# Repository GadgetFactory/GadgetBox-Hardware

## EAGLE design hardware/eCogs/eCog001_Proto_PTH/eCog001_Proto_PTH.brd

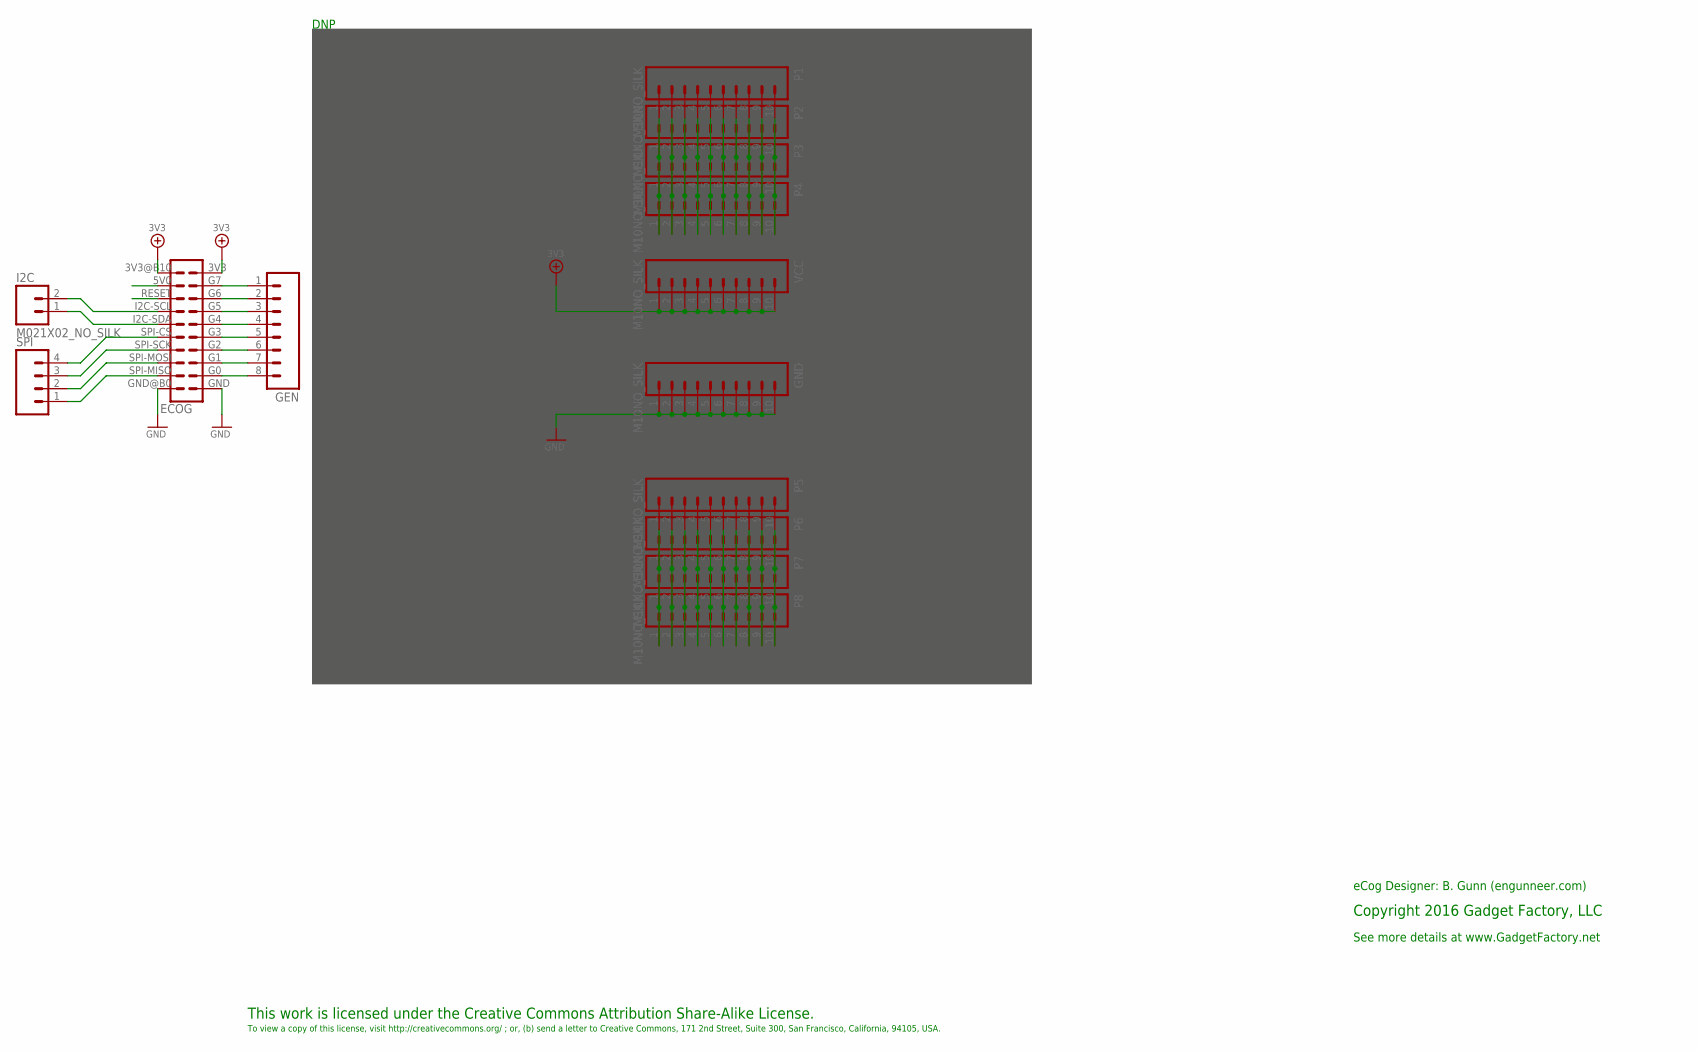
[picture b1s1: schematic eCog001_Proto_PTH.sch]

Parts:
ECOG: ECOG_DUALTHROUGHHOLE; ECOG_DUAL_TH
GEN: M08NO_SILK; 1X08_NO_SILK
GND: M10NO_SILK; 1X10_NO_SILK
I2C: M021X02_NO_SILK; 1X02_NO_SILK
P1, P2, P3, P4, P5, P6, P7, P8: M10NO_SILK; 1X10_NO_SILK
SPI: M041X04_NO_SILK; 1X04_NO_SILK
VCC: M10NO_SILK; 1X10_NO_SILK

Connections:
3V3: ECOG.3V3, ECOG.3V3@B10 (3V3), VCC.1, VCC.2, VCC.3, VCC.4, VCC.5, VCC.6, VCC.7, VCC.8, VCC.9, VCC.10
GND: ECOG.GND, ECOG.GND@B0 (GND), GND.1, GND.2, GND.3, GND.4, GND.5, GND.6, GND.7, GND.8, GND.9, GND.10
unnamed: ECOG.G7, GEN.1
unnamed: ECOG.G6, GEN.2
unnamed: ECOG.G5, GEN.3
unnamed: ECOG.G4, GEN.4
unnamed: ECOG.G3, GEN.5
unnamed: ECOG.G2, GEN.6
unnamed: ECOG.G1, GEN.7
unnamed: ECOG.G0, GEN.8
unnamed: ECOG.SPI-MISO, SPI.1
unnamed: ECOG.SPI-MOSI, SPI.2
unnamed: ECOG.SPI-SCK, SPI.3
unnamed: ECOG.SPI-CS, SPI.4
unnamed: ECOG.I2C-SDA, I2C.1
unnamed: ECOG.I2C-SCL, I2C.2
unnamed: P1.2, P2.2, P3.2, P4.2
unnamed: P1.3, P2.3, P3.3, P4.3
unnamed: P1.4, P2.4, P3.4, P4.4
unnamed: P1.5, P2.5, P3.5, P4.5
unnamed: P1.6, P2.6, P3.6, P4.6
unnamed: P1.7, P2.7, P3.7, P4.7
unnamed: P1.8, P2.8, P3.8, P4.8
unnamed: P1.9, P2.9, P3.9, P4.9
unnamed: P1.10, P2.10, P3.10, P4.10
unnamed: P1.1, P2.1, P3.1, P4.1
unnamed: P5.1, P6.1, P7.1, P8.1
unnamed: P5.2, P6.2, P7.2, P8.2
unnamed: P5.3, P6.3, P7.3, P8.3
unnamed: P5.4, P6.4, P7.4, P8.4
unnamed: P5.5, P6.5, P7.5, P8.5
unnamed: P5.6, P6.6, P7.6, P8.6
unnamed: P5.7, P6.7, P7.7, P8.7
unnamed: P5.8, P6.8, P7.8, P8.8
unnamed: P5.9, P6.9, P7.9, P8.9
unnamed: P5.10, P6.10, P7.10, P8.10

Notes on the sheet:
This work is licensed under the Creative Commons Attribution Share-Alike License.
To view a copy of this license, visit http://creativecommons.org/ ; or, (b) send a letter to Creative Commons, 171 2nd Street, Suite 300, San Francisco, California, 94105, USA.
Copyright 2016 Gadget Factory, LLC
See more details at www.GadgetFactory.net
eCog Designer: B. Gunn (engunneer.com)
DNP

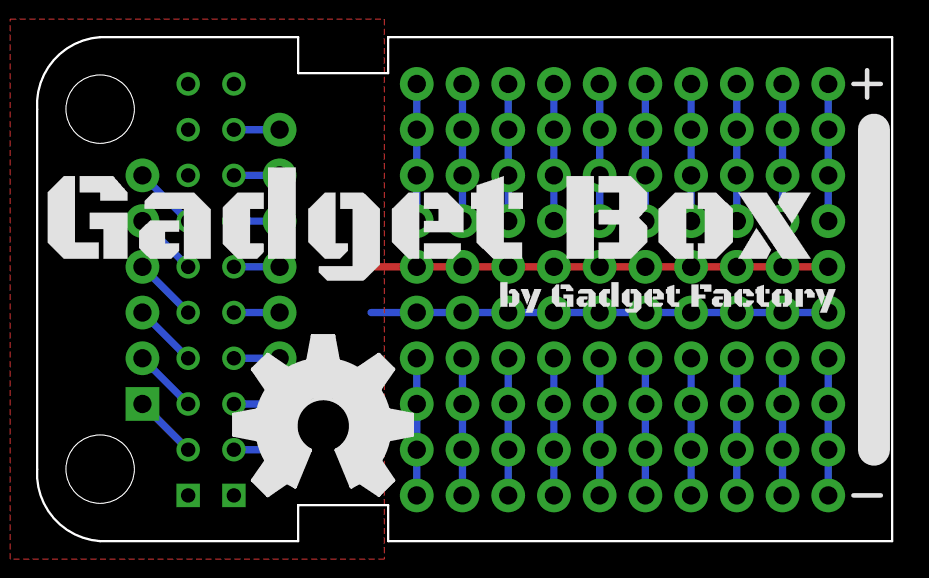
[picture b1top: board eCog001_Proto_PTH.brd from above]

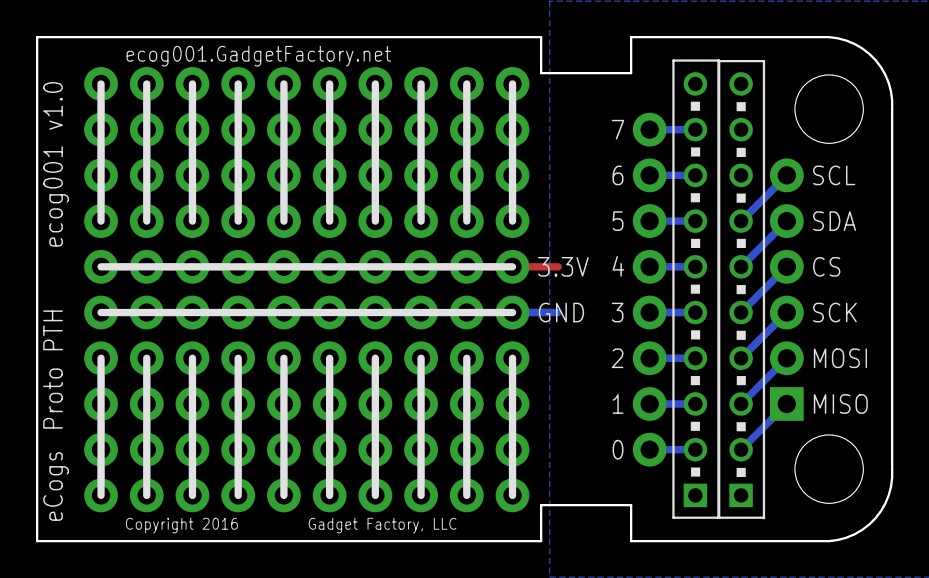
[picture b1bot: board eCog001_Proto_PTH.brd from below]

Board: 2 copper layers, 47.5 x 28.0 mm, 16 parts (2 on the bottom side), 36 nets.

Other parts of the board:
U$1: GADGETBOX_TEXT
U$10: OSHW_FILLX350_NOTEXT

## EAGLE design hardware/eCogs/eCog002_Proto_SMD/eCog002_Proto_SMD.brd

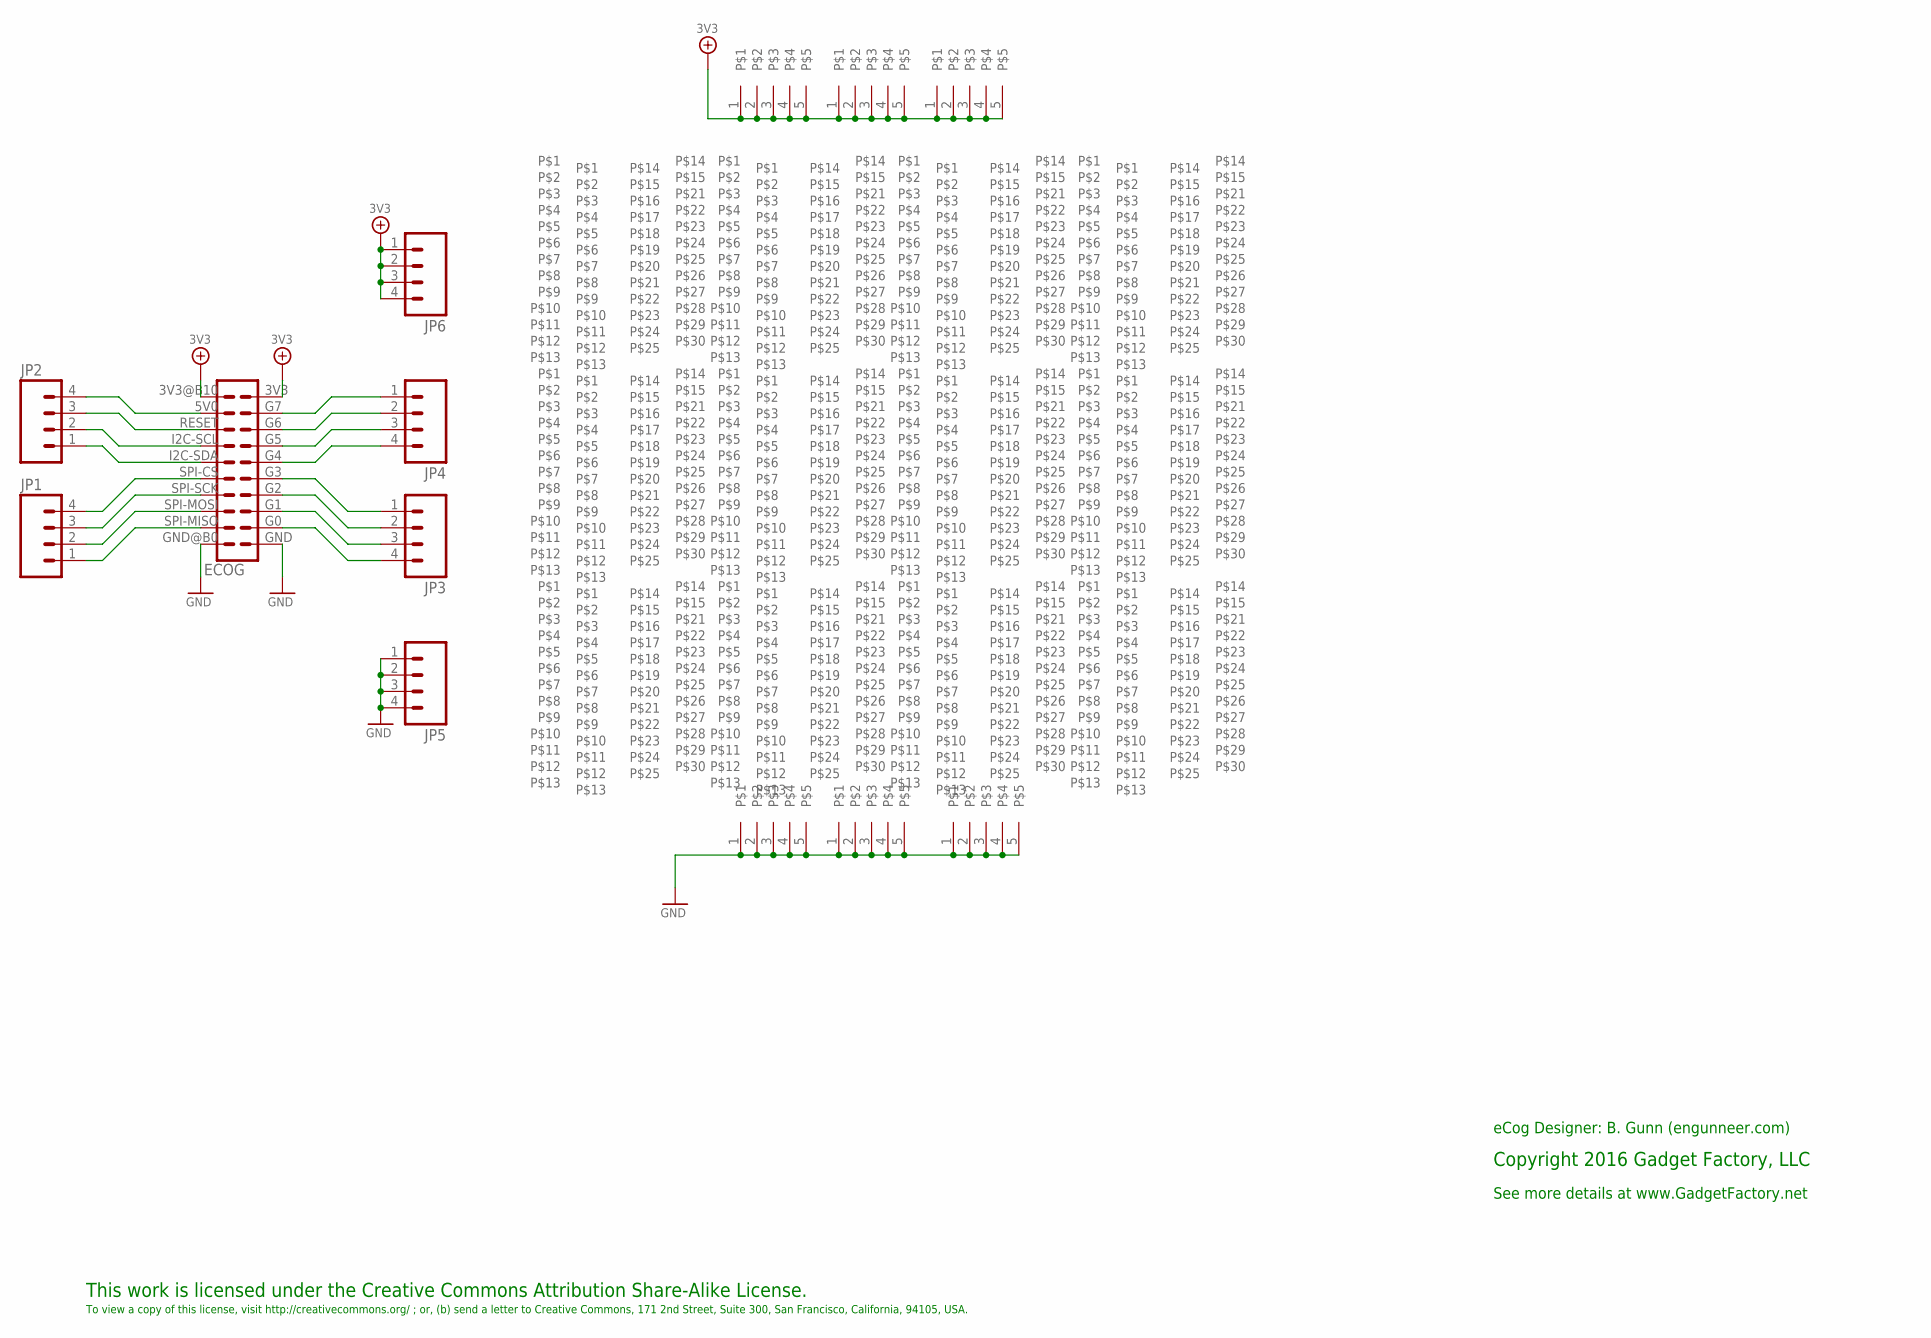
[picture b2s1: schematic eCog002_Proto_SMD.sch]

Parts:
ECOG: ECOG_DUALTHROUGHHOLE; ECOG_DUAL_TH
JP1, JP2, JP3, JP4, JP5, JP6: M041.27MM; 1X04-1.27MM
U$2, U$3, U$4, U$5, U$6, U$7, U$8, U$9, U$11, U$12, U$13, U$14: SMD_PROTO_2550X65; SMD-5065
U$15, U$16, U$17, U$18, U$19, U$20: SMD_PROTO_55; SMD-5065-5

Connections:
3V3: ECOG.3V3, ECOG.3V3@B10 (3V3), JP6.1, JP6.2, JP6.3, JP6.4, U$15.1, U$15.2, U$15.3, U$15.4, U$15.5, U$16.1, U$16.2, U$16.3, U$16.4, U$16.5, U$17.1, U$17.2, U$17.3, U$17.4, U$17.5
GND: ECOG.GND, ECOG.GND@B0 (GND), JP5.1, JP5.2, JP5.3, JP5.4, U$18.1, U$18.2, U$18.3, U$18.4, U$18.5, U$19.1, U$19.2, U$19.3, U$19.4, U$19.5, U$20.1, U$20.2, U$20.3, U$20.4, U$20.5
unnamed: ECOG.G7, JP4.1
unnamed: ECOG.G6, JP4.2
unnamed: ECOG.G5, JP4.3
unnamed: ECOG.G4, JP4.4
unnamed: ECOG.G3, JP3.1
unnamed: ECOG.G2, JP3.2
unnamed: ECOG.G1, JP3.3
unnamed: ECOG.G0, JP3.4
unnamed: ECOG.SPI-MISO, JP1.1
unnamed: ECOG.SPI-MOSI, JP1.2
unnamed: ECOG.SPI-SCK, JP1.3
unnamed: ECOG.SPI-CS, JP1.4
unnamed: ECOG.I2C-SDA, JP2.1
unnamed: ECOG.I2C-SCL, JP2.2
unnamed: ECOG.RESET, JP2.3
unnamed: ECOG.5V0 (5V), JP2.4

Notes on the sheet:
This work is licensed under the Creative Commons Attribution Share-Alike License.
To view a copy of this license, visit http://creativecommons.org/ ; or, (b) send a letter to Creative Commons, 171 2nd Street, Suite 300, San Francisco, California, 94105, USA.
Copyright 2016 Gadget Factory, LLC
See more details at www.GadgetFactory.net
eCog Designer: B. Gunn (engunneer.com)

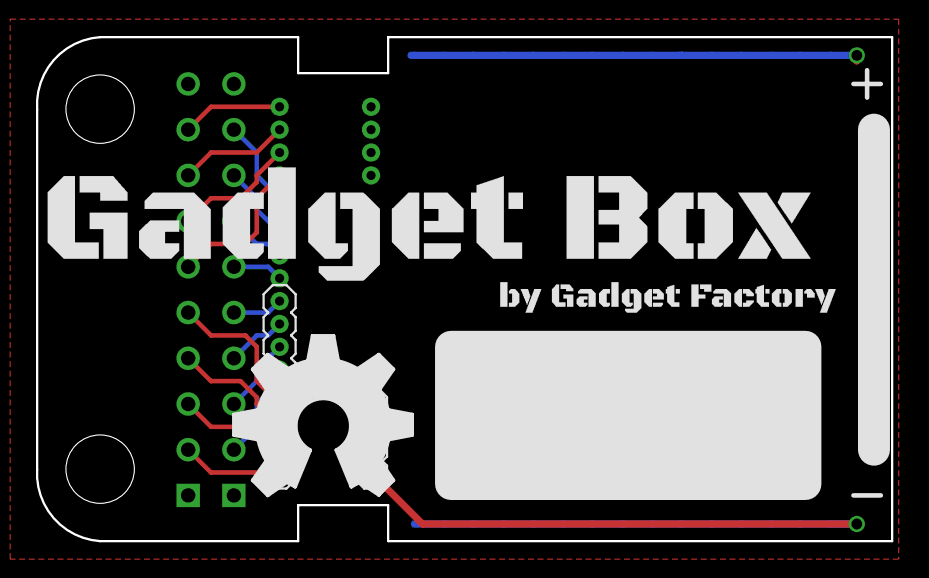
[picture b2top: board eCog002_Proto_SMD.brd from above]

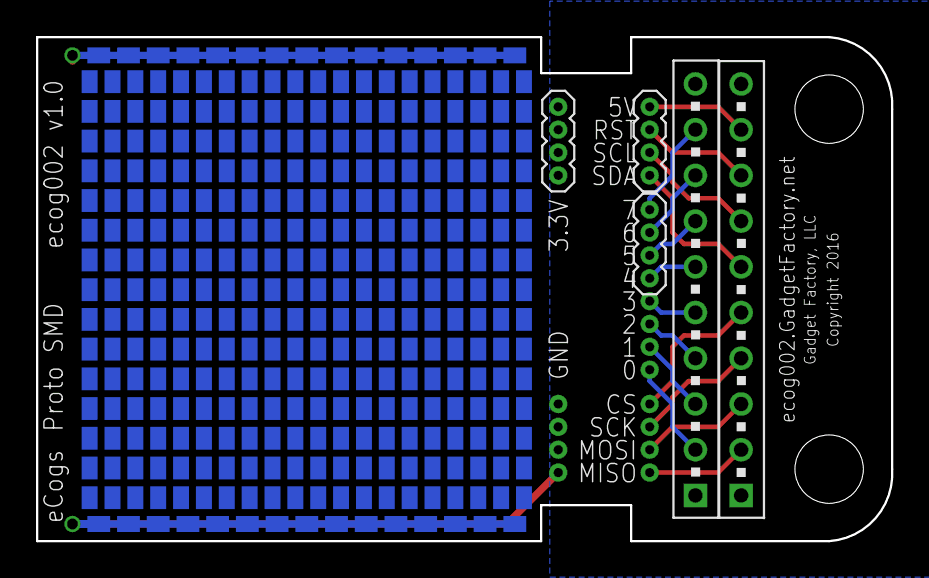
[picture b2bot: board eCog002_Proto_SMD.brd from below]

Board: 2 copper layers, 47.5 x 28.0 mm, 27 parts (21 on the bottom side), 18 nets.

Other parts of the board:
U$1: GADGETBOX_TEXT
U$10: OSHW_FILLX350_NOTEXT

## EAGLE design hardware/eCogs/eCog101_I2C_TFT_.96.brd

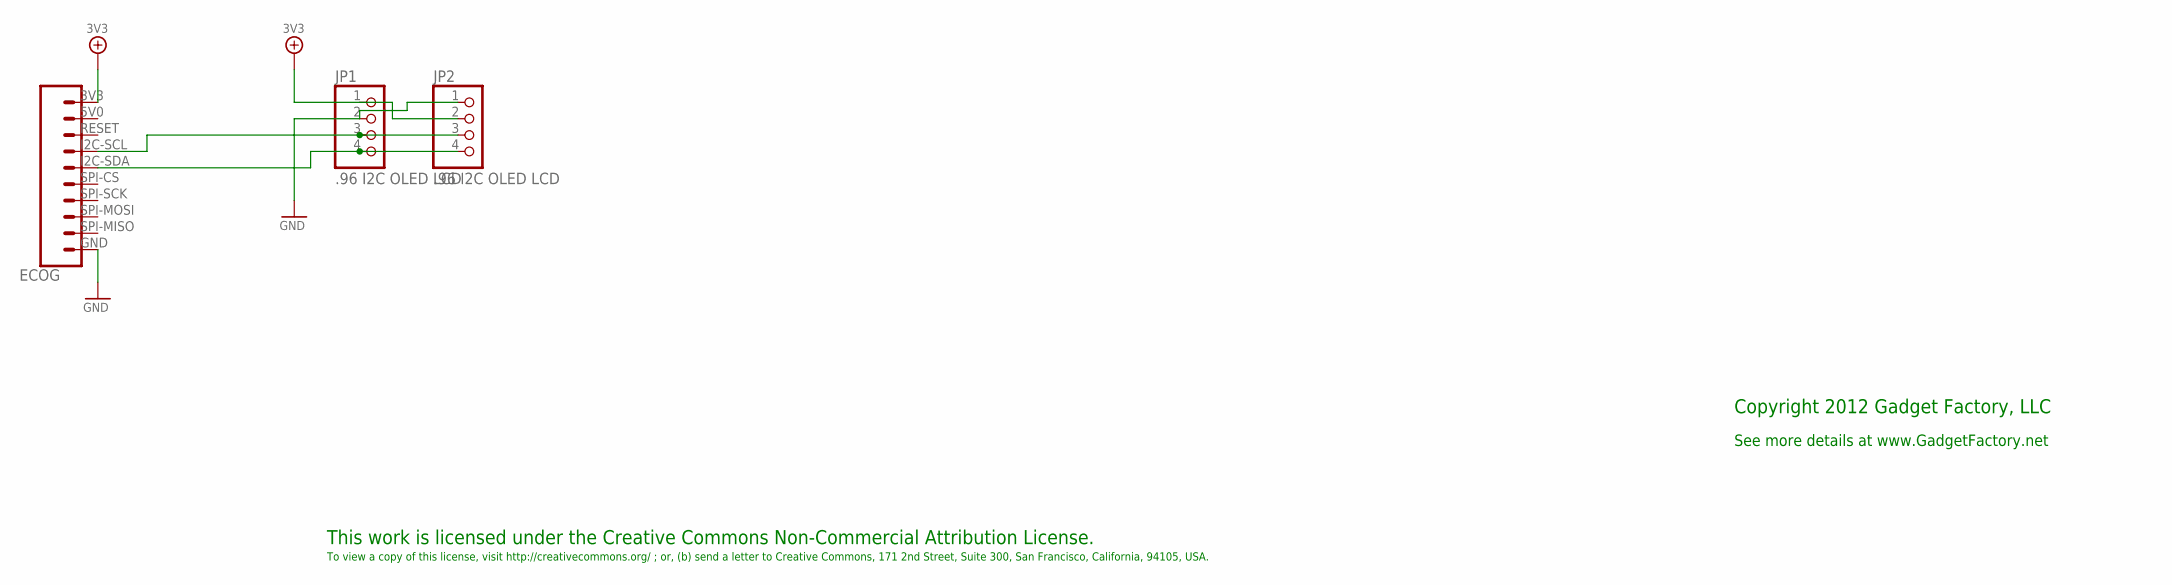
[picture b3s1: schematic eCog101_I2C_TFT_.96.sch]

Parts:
ECOG: ECOG_BUSES_ROWTHROUGHHOLE; ECOG_BUSES_TH
JP1, JP2: .96 I2C OLED LCD; 1X04

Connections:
3V3: ECOG.3V3, JP1.1, JP2.2
GND: ECOG.GND, JP1.2, JP2.1
unnamed: ECOG.I2C-SCL, JP1.3, JP2.3
unnamed: ECOG.I2C-SDA, JP1.4, JP2.4

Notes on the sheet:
This work is licensed under the Creative Commons Non-Commercial Attribution License.
To view a copy of this license, visit http://creativecommons.org/ ; or, (b) send a letter to Creative Commons, 171 2nd Street, Suite 300, San Francisco, California, 94105, USA.
Copyright 2012 Gadget Factory, LLC
See more details at www.GadgetFactory.net

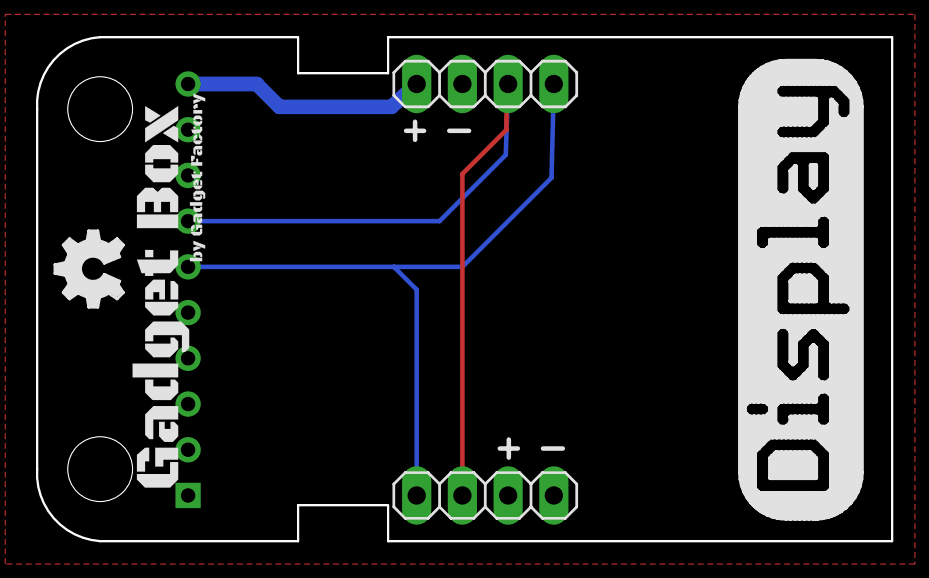
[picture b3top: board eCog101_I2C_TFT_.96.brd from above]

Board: 2 copper layers, 47.5 x 28.0 mm, 5 parts (0 on the bottom side), 4 nets.

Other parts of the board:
U$1: GADGETBOX_SMALL
U$2: OSHW_FILLX150_NOTEXT

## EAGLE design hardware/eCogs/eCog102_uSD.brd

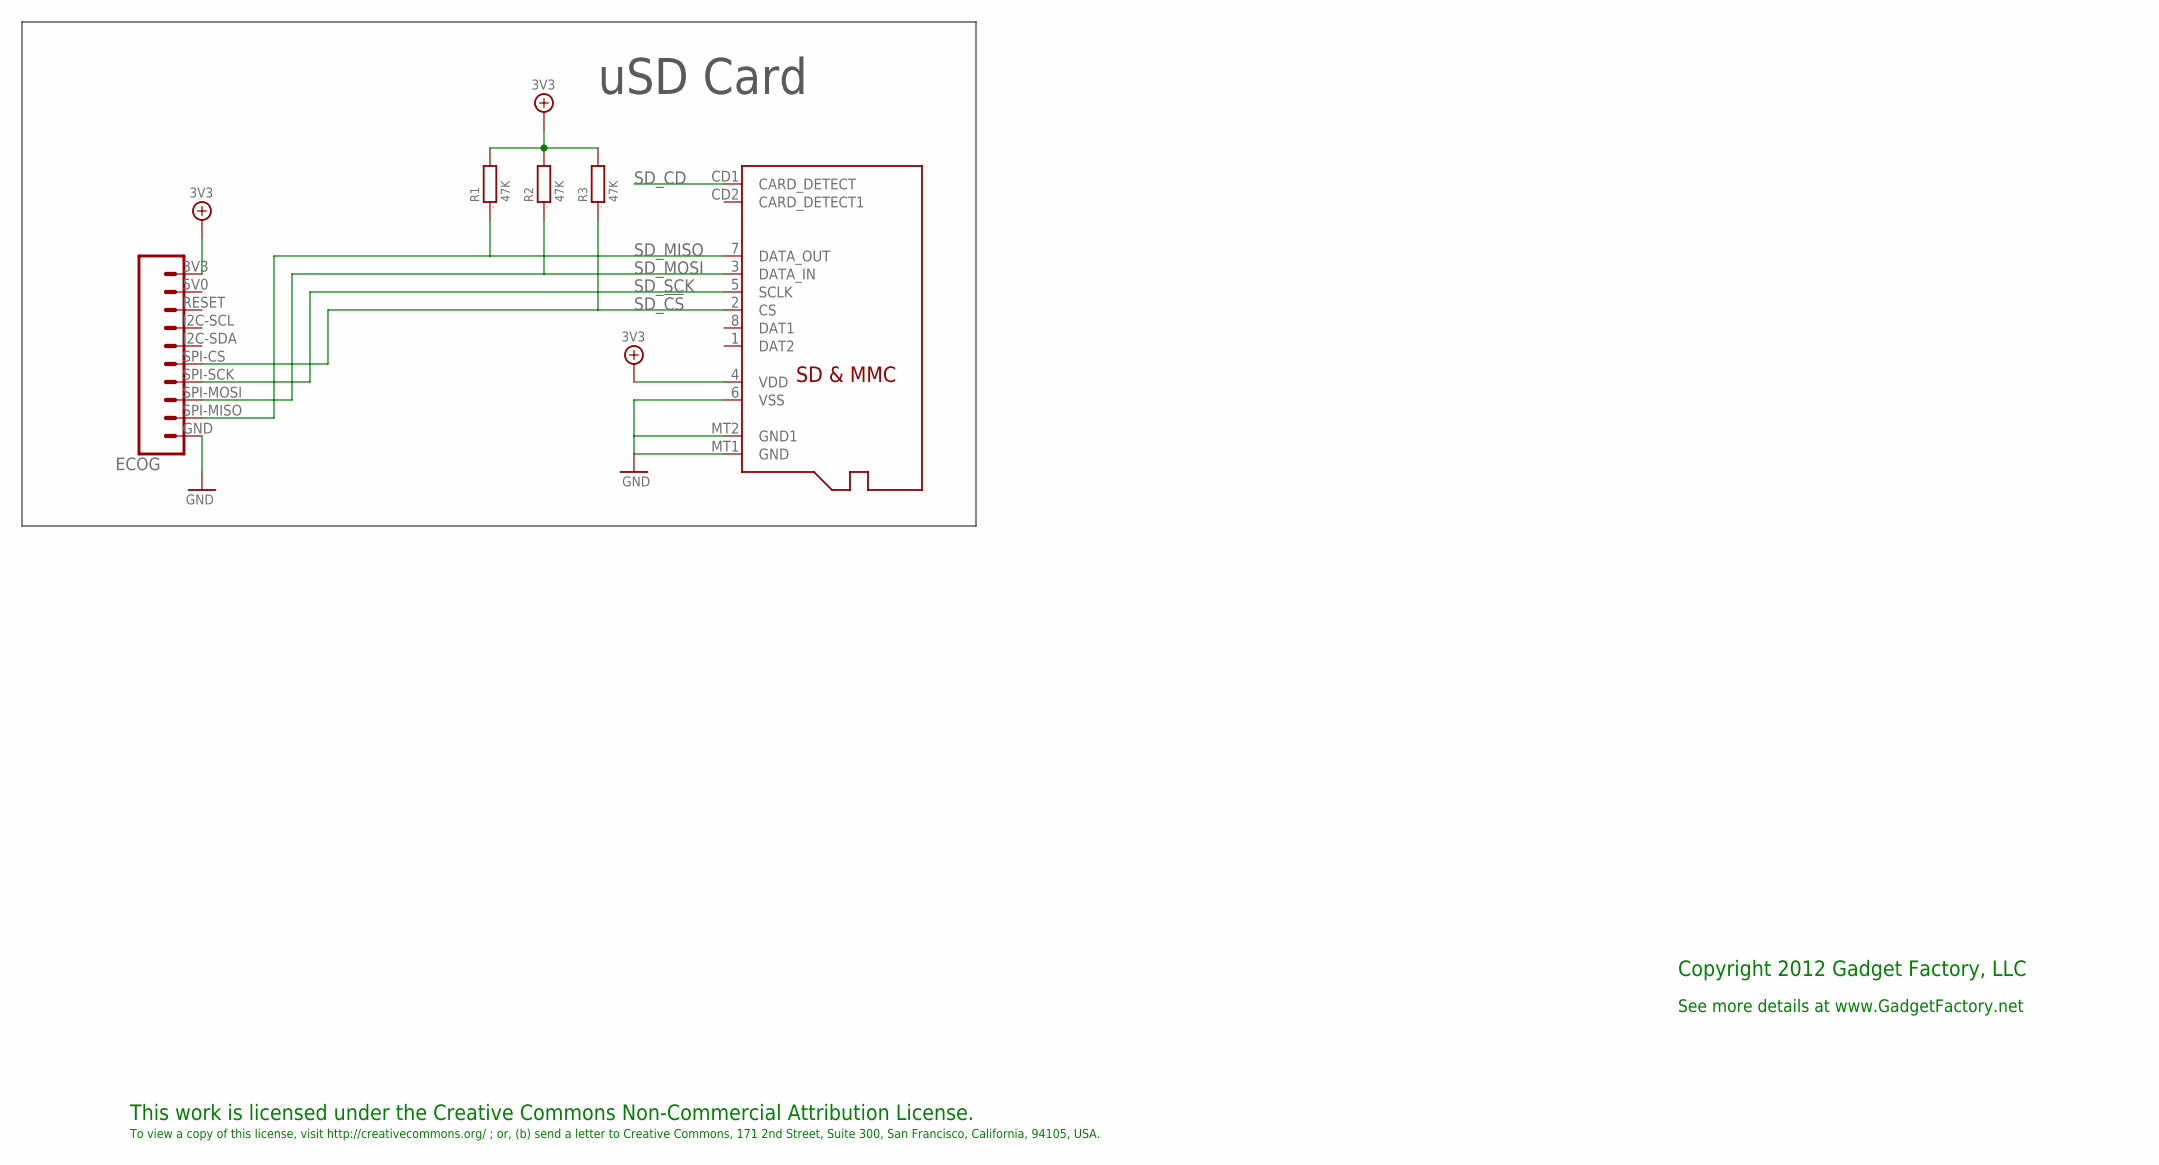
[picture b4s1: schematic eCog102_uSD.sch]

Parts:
ECOG: ECOG_BUSES_ROWTHROUGHHOLE; ECOG_BUSES_TH
R1, R2, R3: 47K; 0805; PARTNO RMCF0805JT47K0; DIGIKEY RMCF0805JT47K0CT-ND
SD1: MICROSD; PARTNO 101-00660-68-6; DIGIKEY 101-00660-68-6-1-ND

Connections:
3V3: ECOG.3V3, R1.2, R2.2, R3.2, SD1.4 (VDD)
GND: ECOG.GND, SD1.6 (VSS), SD1.MT1 (GND), SD1.MT2 (GND1)
SD_!CS: ECOG.SPI-CS, R3.1, SD1.2 (CS)
SD_CD: SD1.CD1 (CARD_DETECT)
SD_MISO: ECOG.SPI-MISO, R1.1, SD1.7 (DATA_OUT)
SD_MOSI: ECOG.SPI-MOSI, R2.1, SD1.3 (DATA_IN)
SD_SCK: ECOG.SPI-SCK, SD1.5 (SCLK)

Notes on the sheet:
This work is licensed under the Creative Commons Non-Commercial Attribution License.
To view a copy of this license, visit http://creativecommons.org/ ; or, (b) send a letter to Creative Commons, 171 2nd Street, Suite 300, San Francisco, California, 94105, USA.
Copyright 2012 Gadget Factory, LLC
See more details at www.GadgetFactory.net
uSD Card

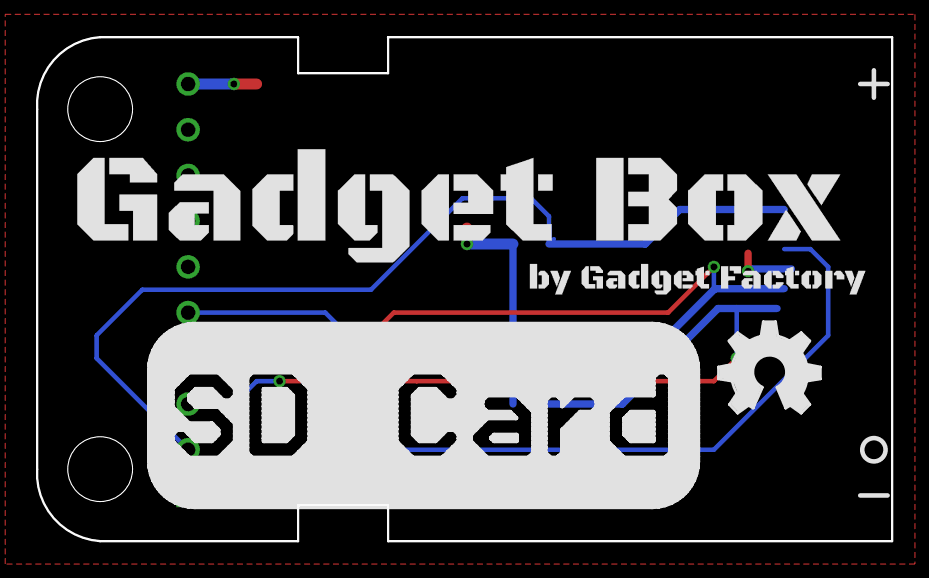
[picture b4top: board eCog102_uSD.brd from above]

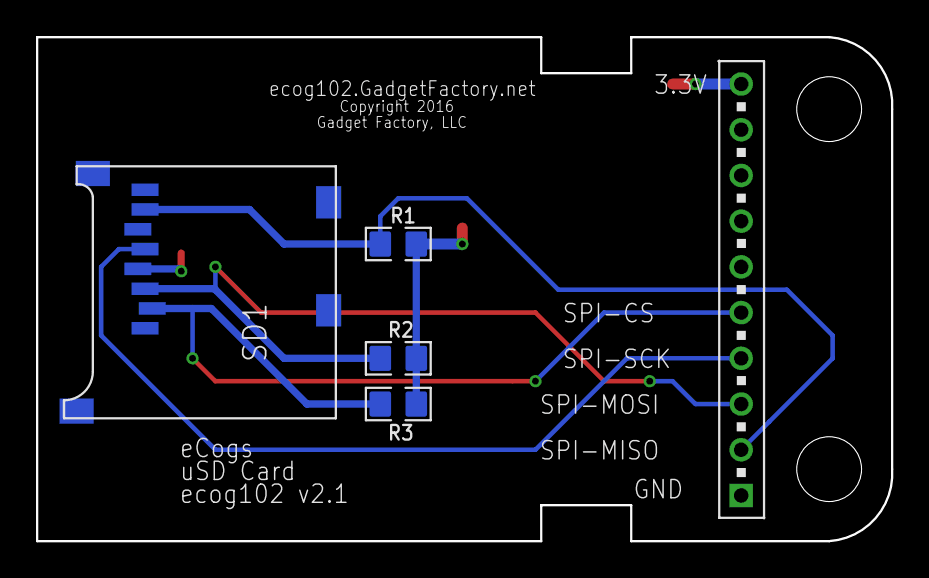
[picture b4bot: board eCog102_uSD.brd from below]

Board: 2 copper layers, 47.5 x 28.0 mm, 7 parts (4 on the bottom side), 6 nets.

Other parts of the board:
U$1: GADGETBOX_TEXT
U$2: OSHW_FILLX200_NOTEXT

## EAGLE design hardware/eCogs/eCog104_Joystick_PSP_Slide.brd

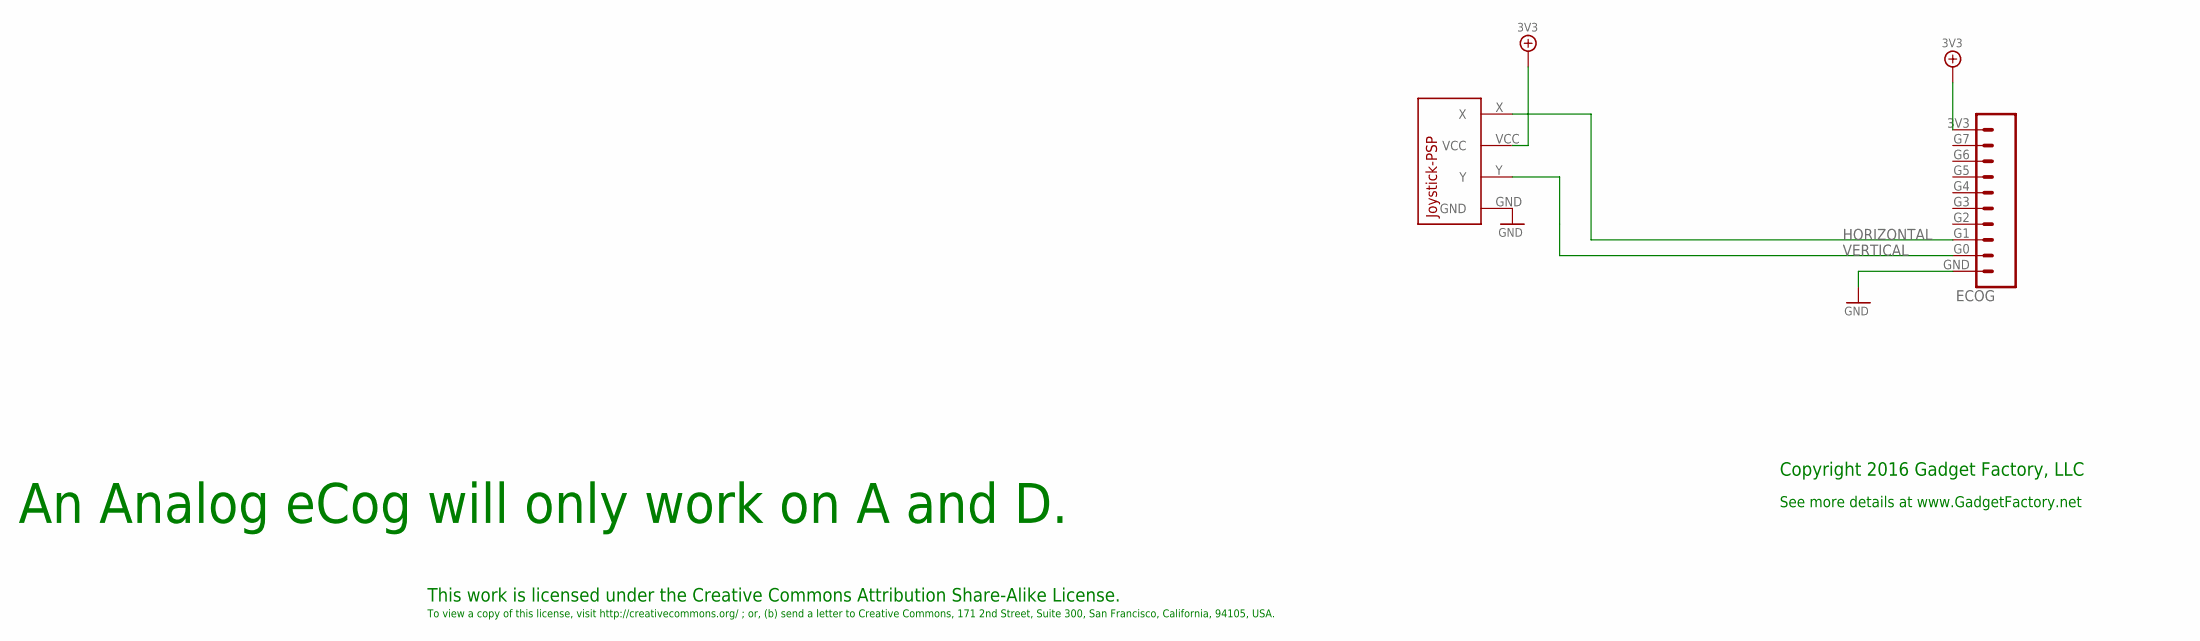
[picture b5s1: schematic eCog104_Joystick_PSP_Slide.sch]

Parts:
ECOG: ECOG_GENERAL_ROWTHROUGHOLE; ECOG_GENERAL_TH
U$4: JOYSTICK-PSP1000

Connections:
3V3: ECOG.3V3, U$4.VCC
GND: ECOG.GND, U$4.GND
HORIZONTAL: ECOG.G1, U$4.X
VERTICAL: ECOG.G0, U$4.Y

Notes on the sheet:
This work is licensed under the Creative Commons Attribution Share-Alike License.
To view a copy of this license, visit http://creativecommons.org/ ; or, (b) send a letter to Creative Commons, 171 2nd Street, Suite 300, San Francisco, California, 94105, USA.
Copyright 2016 Gadget Factory, LLC
See more details at www.GadgetFactory.net
An Analog eCog will only work on A and D.

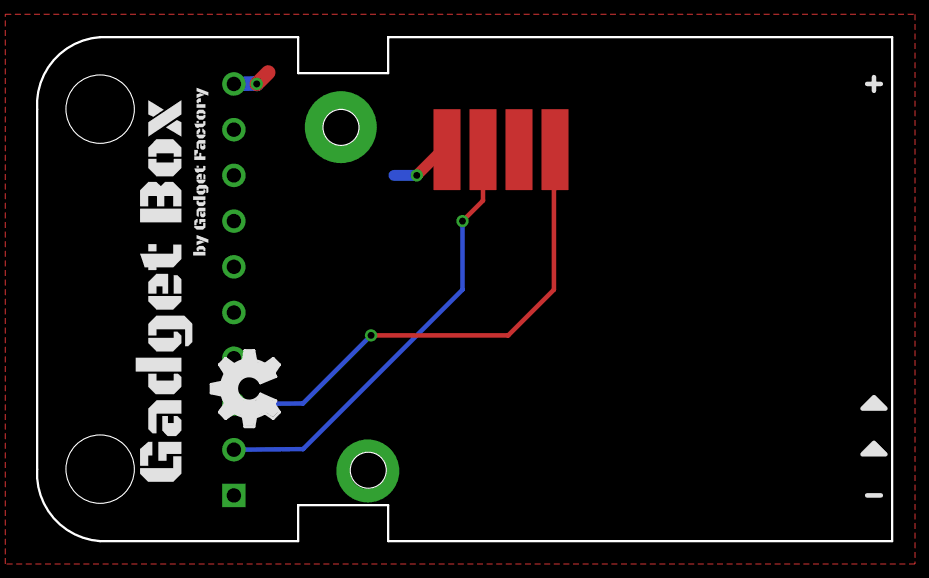
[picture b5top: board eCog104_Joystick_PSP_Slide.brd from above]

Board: 2 copper layers, 47.5 x 28.0 mm, 6 parts (0 on the bottom side), 4 nets.

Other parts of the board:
U$1, U$2: LEGEND_ANALOG
U$3: GADGETBOX_SMALL
U$5: OSHW_FILLX150_NOTEXT

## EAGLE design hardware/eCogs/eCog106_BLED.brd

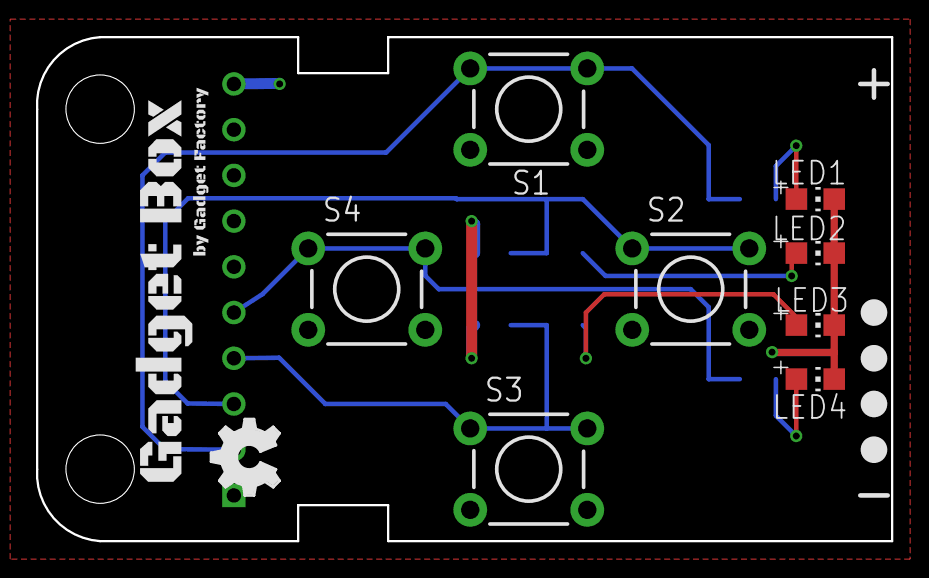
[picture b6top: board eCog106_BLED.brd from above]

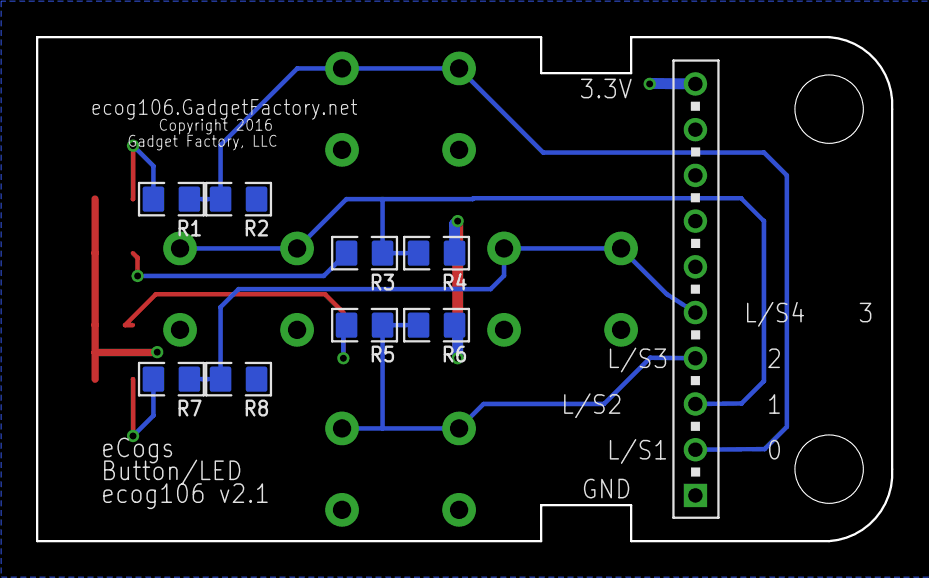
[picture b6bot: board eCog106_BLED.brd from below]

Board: 2 copper layers, 47.5 x 28.0 mm, 23 parts (8 on the bottom side), 10 nets.

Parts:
ECOG: ECOG_GENERAL_ROWTHROUGHOLE; ECOG_GENERAL_TH
LED1, LED2, LED3, LED4: CHIP-LED0805
R1, R3, R5, R7: 390; 0805
R2, R4, R6, R8: 10K; 0805
S1, S2, S3, S4: TACTILE-PTH
U$1, U$2, U$3, U$4: LEGEND_DIO
U$5: GADGETBOX_SMALL
U$6: OSHW_FILLX150_NOTEXT

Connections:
1: ECOG.G0, R1.1, R2.2, S1.1, S1.2
2: ECOG.G1, R3.1, R4.2, S2.1, S2.2
3: ECOG.G2, R5.1, R6.2, S3.1, S3.2
3V3: ECOG.3V3, S1.3, S1.4, S2.3, S2.4, S3.3, S3.4, S4.3, S4.4
4: ECOG.G3, R7.1, R8.2, S4.1, S4.2
GND: ECOG.GND, LED1.C, LED2.C, LED3.C, LED4.C, R2.1, R4.1, R6.1, R8.1
unnamed: LED1.A, R1.2
unnamed: LED2.A, R3.2
unnamed: LED3.A, R5.2
unnamed: LED4.A, R7.2

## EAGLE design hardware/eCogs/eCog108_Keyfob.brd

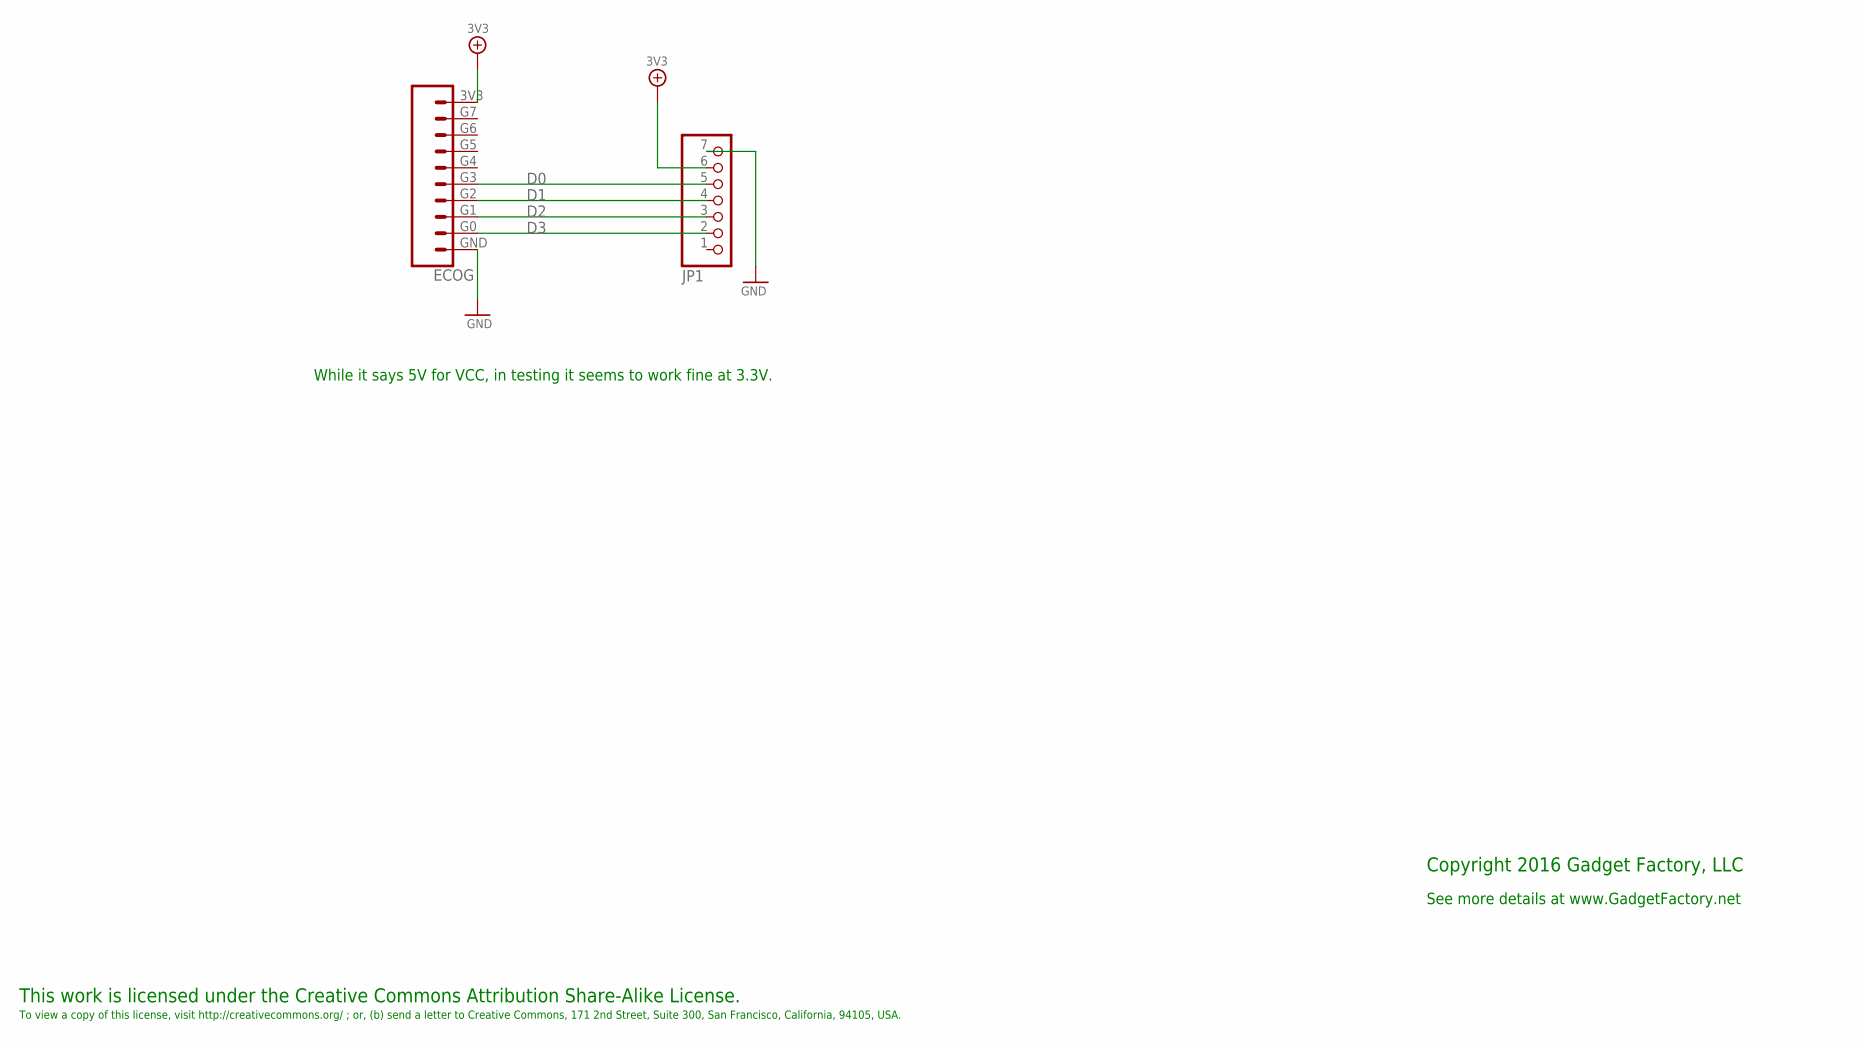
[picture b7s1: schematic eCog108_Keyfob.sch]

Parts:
ECOG: ECOG_GENERAL_ROWTHROUGHOLE; ECOG_GENERAL_TH
JP1: PINHD-1X7; 1X07

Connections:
3V3: ECOG.3V3, JP1.6
D0: ECOG.G3, JP1.5
D1: ECOG.G2, JP1.4
D2: ECOG.G1, JP1.3
D3: ECOG.G0, JP1.2
GND: ECOG.GND, JP1.7

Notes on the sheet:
This work is licensed under the Creative Commons Attribution Share-Alike License.
To view a copy of this license, visit http://creativecommons.org/ ; or, (b) send a letter to Creative Commons, 171 2nd Street, Suite 300, San Francisco, California, 94105, USA.
Copyright 2016 Gadget Factory, LLC
See more details at www.GadgetFactory.net
While it says 5V for VCC, in testing it seems to work fine at 3.3V.

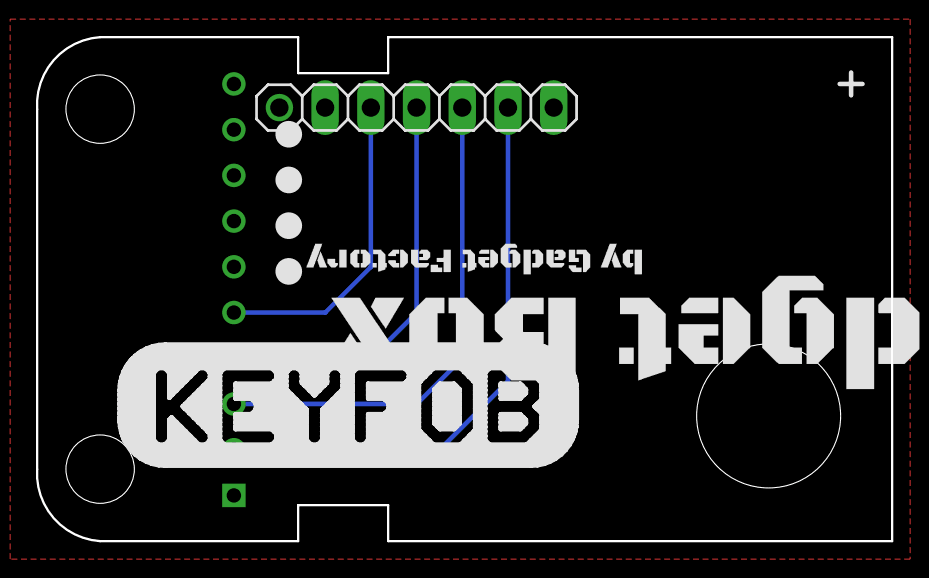
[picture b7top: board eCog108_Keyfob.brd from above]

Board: 2 copper layers, 47.5 x 28.0 mm, 7 parts (0 on the bottom side), 6 nets.

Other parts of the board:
U$1: GADGETBOX_TEXT
U$2, U$3, U$4, U$5: LEGEND_DIO

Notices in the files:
parts and their libraries:
SparkFun-Connectors: Licensing: Creative Commons ShareAlike 4.0 International - https://creativecommons.org/licenses/by-sa/4.0
SparkFun: Licensing: CC v3.0 Share-Alike You are welcome to use this library for commercial purposes.
